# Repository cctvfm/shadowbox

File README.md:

# shadowbox
Shadowbox is an Open Source optically controlled digital drone synth where parameters are controlled by introducing or blocking light. Based on Emilie Gillet's Plaits Module.

To Compile code:

Copy entire 'neuzplaits' folder into the 'eurorack' folder in the mutable dev environment.

run 

make -f neuzplaits/bootloader/makefile hex

make -f neuzplaits/makefile

to upload using ST-Link V2:

make -f neuzplaits/makefile upload

'AVR CHICLET' is an alternate brain board using ATMEGA328P. Code to come.

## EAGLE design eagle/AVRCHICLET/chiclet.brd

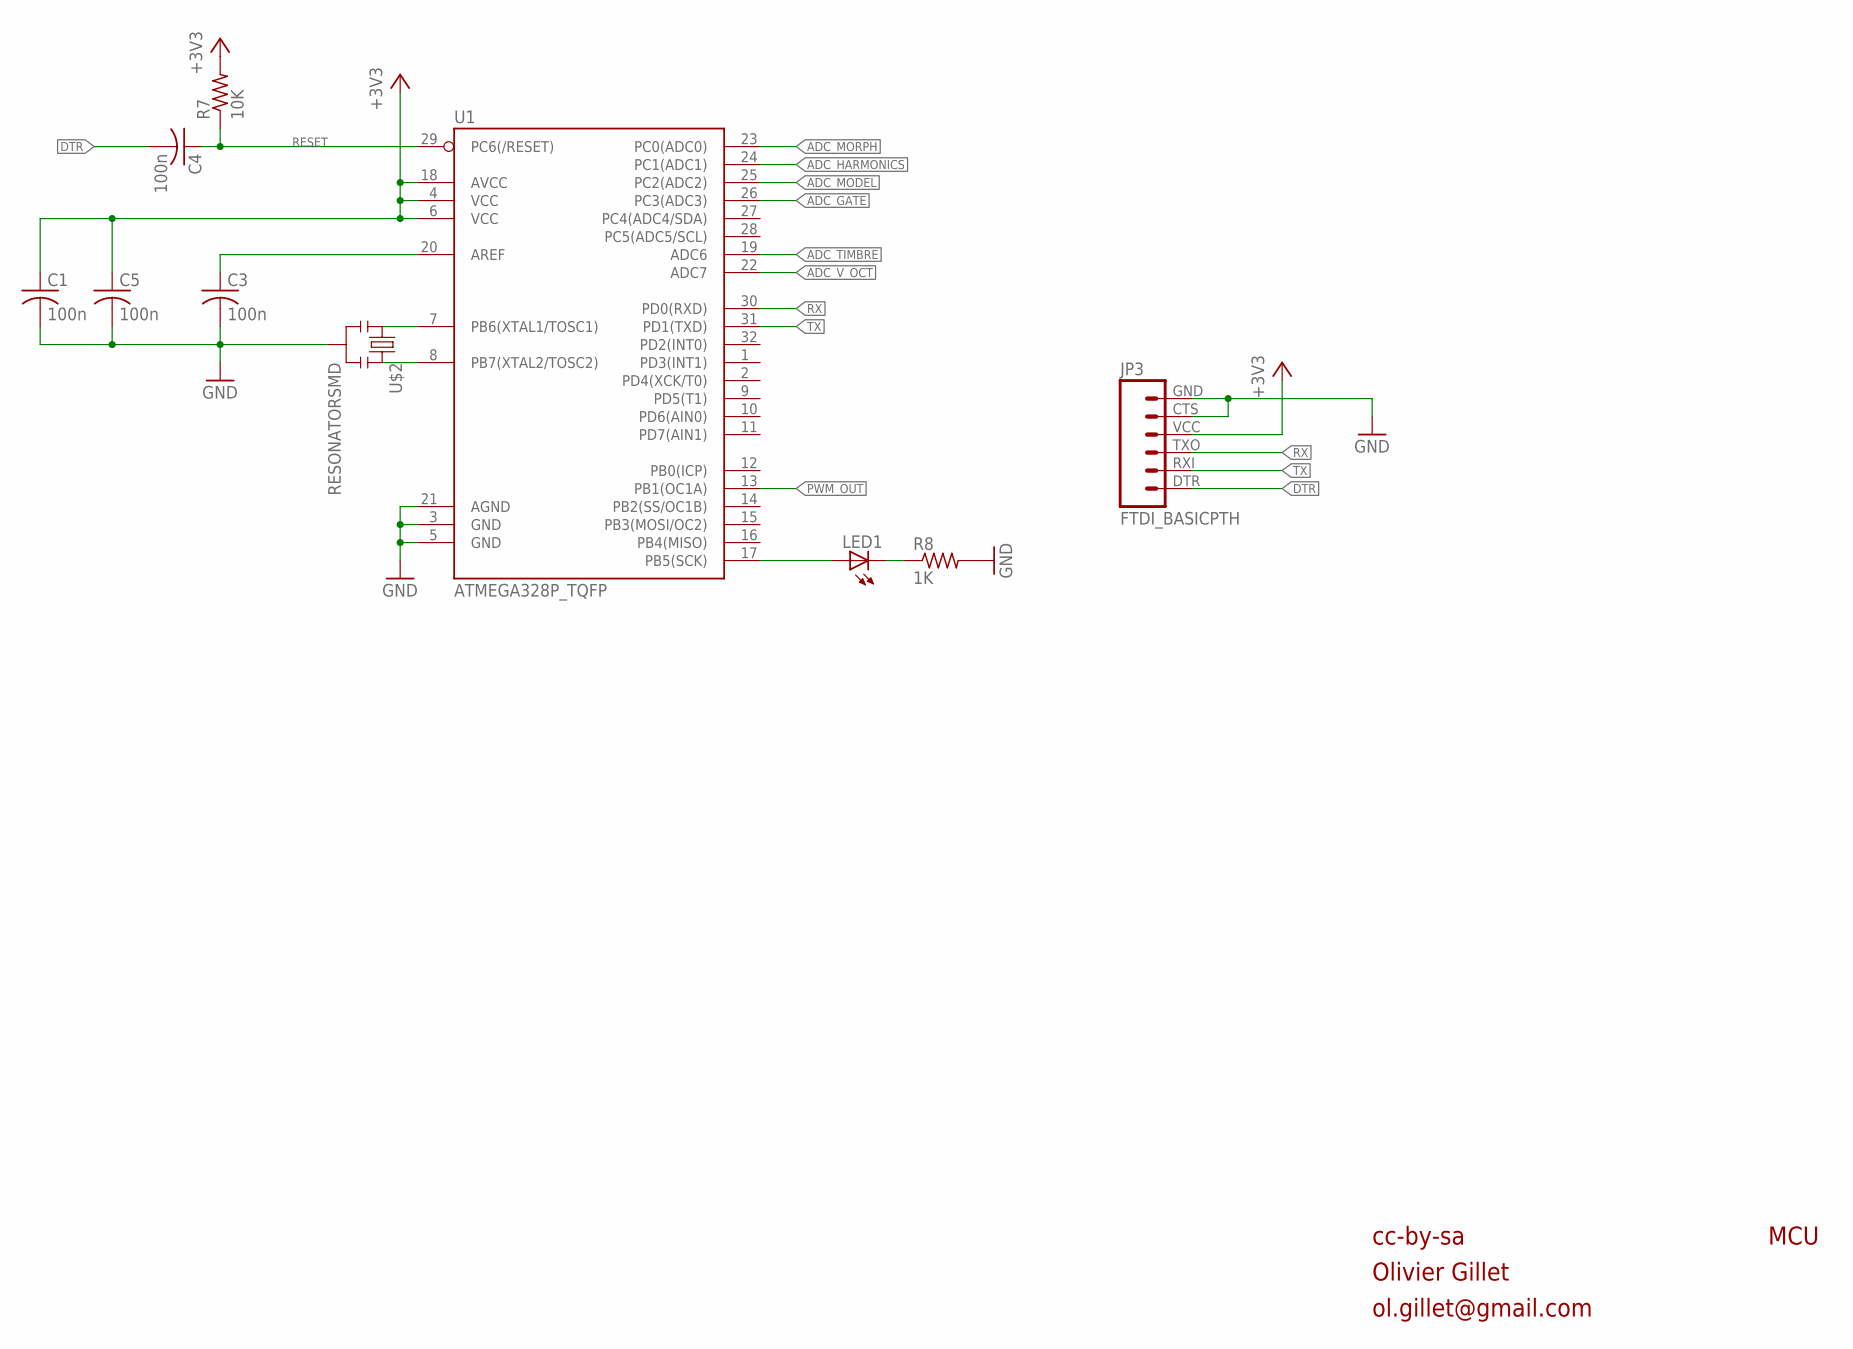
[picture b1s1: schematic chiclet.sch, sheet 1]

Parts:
C1, C3, C4, C5: 100n; C0805
JP3: FTDI_BASICPTH; FTDI_BASIC
LED1: LED-0805; LED-805
R7: 10K; M0805
R8: 1K; M0805
U1: ATMEGA328P_TQFP; TQFP32-08
U$2: RESONATORSMD; RESONATOR-SMD

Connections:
+3V3: C1.1, C5.1, JP3.VCC (4), R7.2, U1.4 (VCC), U1.6 (VCC), U1.18 (AVCC); also elsewhere on the board
ADC_GATE: U1.26 (PC3(ADC3)); also elsewhere on the board
ADC_HARMONICS: U1.24 (PC1(ADC1)); also elsewhere on the board
ADC_MODEL: U1.25 (PC2(ADC2)); also elsewhere on the board
ADC_MORPH: U1.23 (PC0(ADC0)); also elsewhere on the board
ADC_TIMBRE: U1.19 (ADC6); also elsewhere on the board
ADC_V_OCT: U1.22 (ADC7); also elsewhere on the board
DTR: C4.2, JP3.DTR (1)
GND: C1.2, C3.2, C5.2, JP3.CTS (5), JP3.GND (6), R8.2, U1.3 (GND), U1.5 (GND), U1.21 (AGND), U$2.2; also elsewhere on the board
unnamed: U1.7 (PB6(XTAL1/TOSC1)), U$2.1
unnamed: U1.8 (PB7(XTAL2/TOSC2)), U$2.3
unnamed: C3.1, U1.20 (AREF)
unnamed: LED1.A, U1.17 (PB5(SCK))
unnamed: LED1.C, R8.1
PWM_OUT: U1.13 (PB1(OC1A)); also elsewhere on the board
RESET: C4.1, R7.1, U1.29 (PC6(/RESET))
RX: JP3.TXO (3), U1.30 (PD0(RXD))
TX: JP3.RXI (2), U1.31 (PD1(TXD))

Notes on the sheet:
cc-by-sa
Olivier Gillet
ol.gillet@gmail.com
MCU

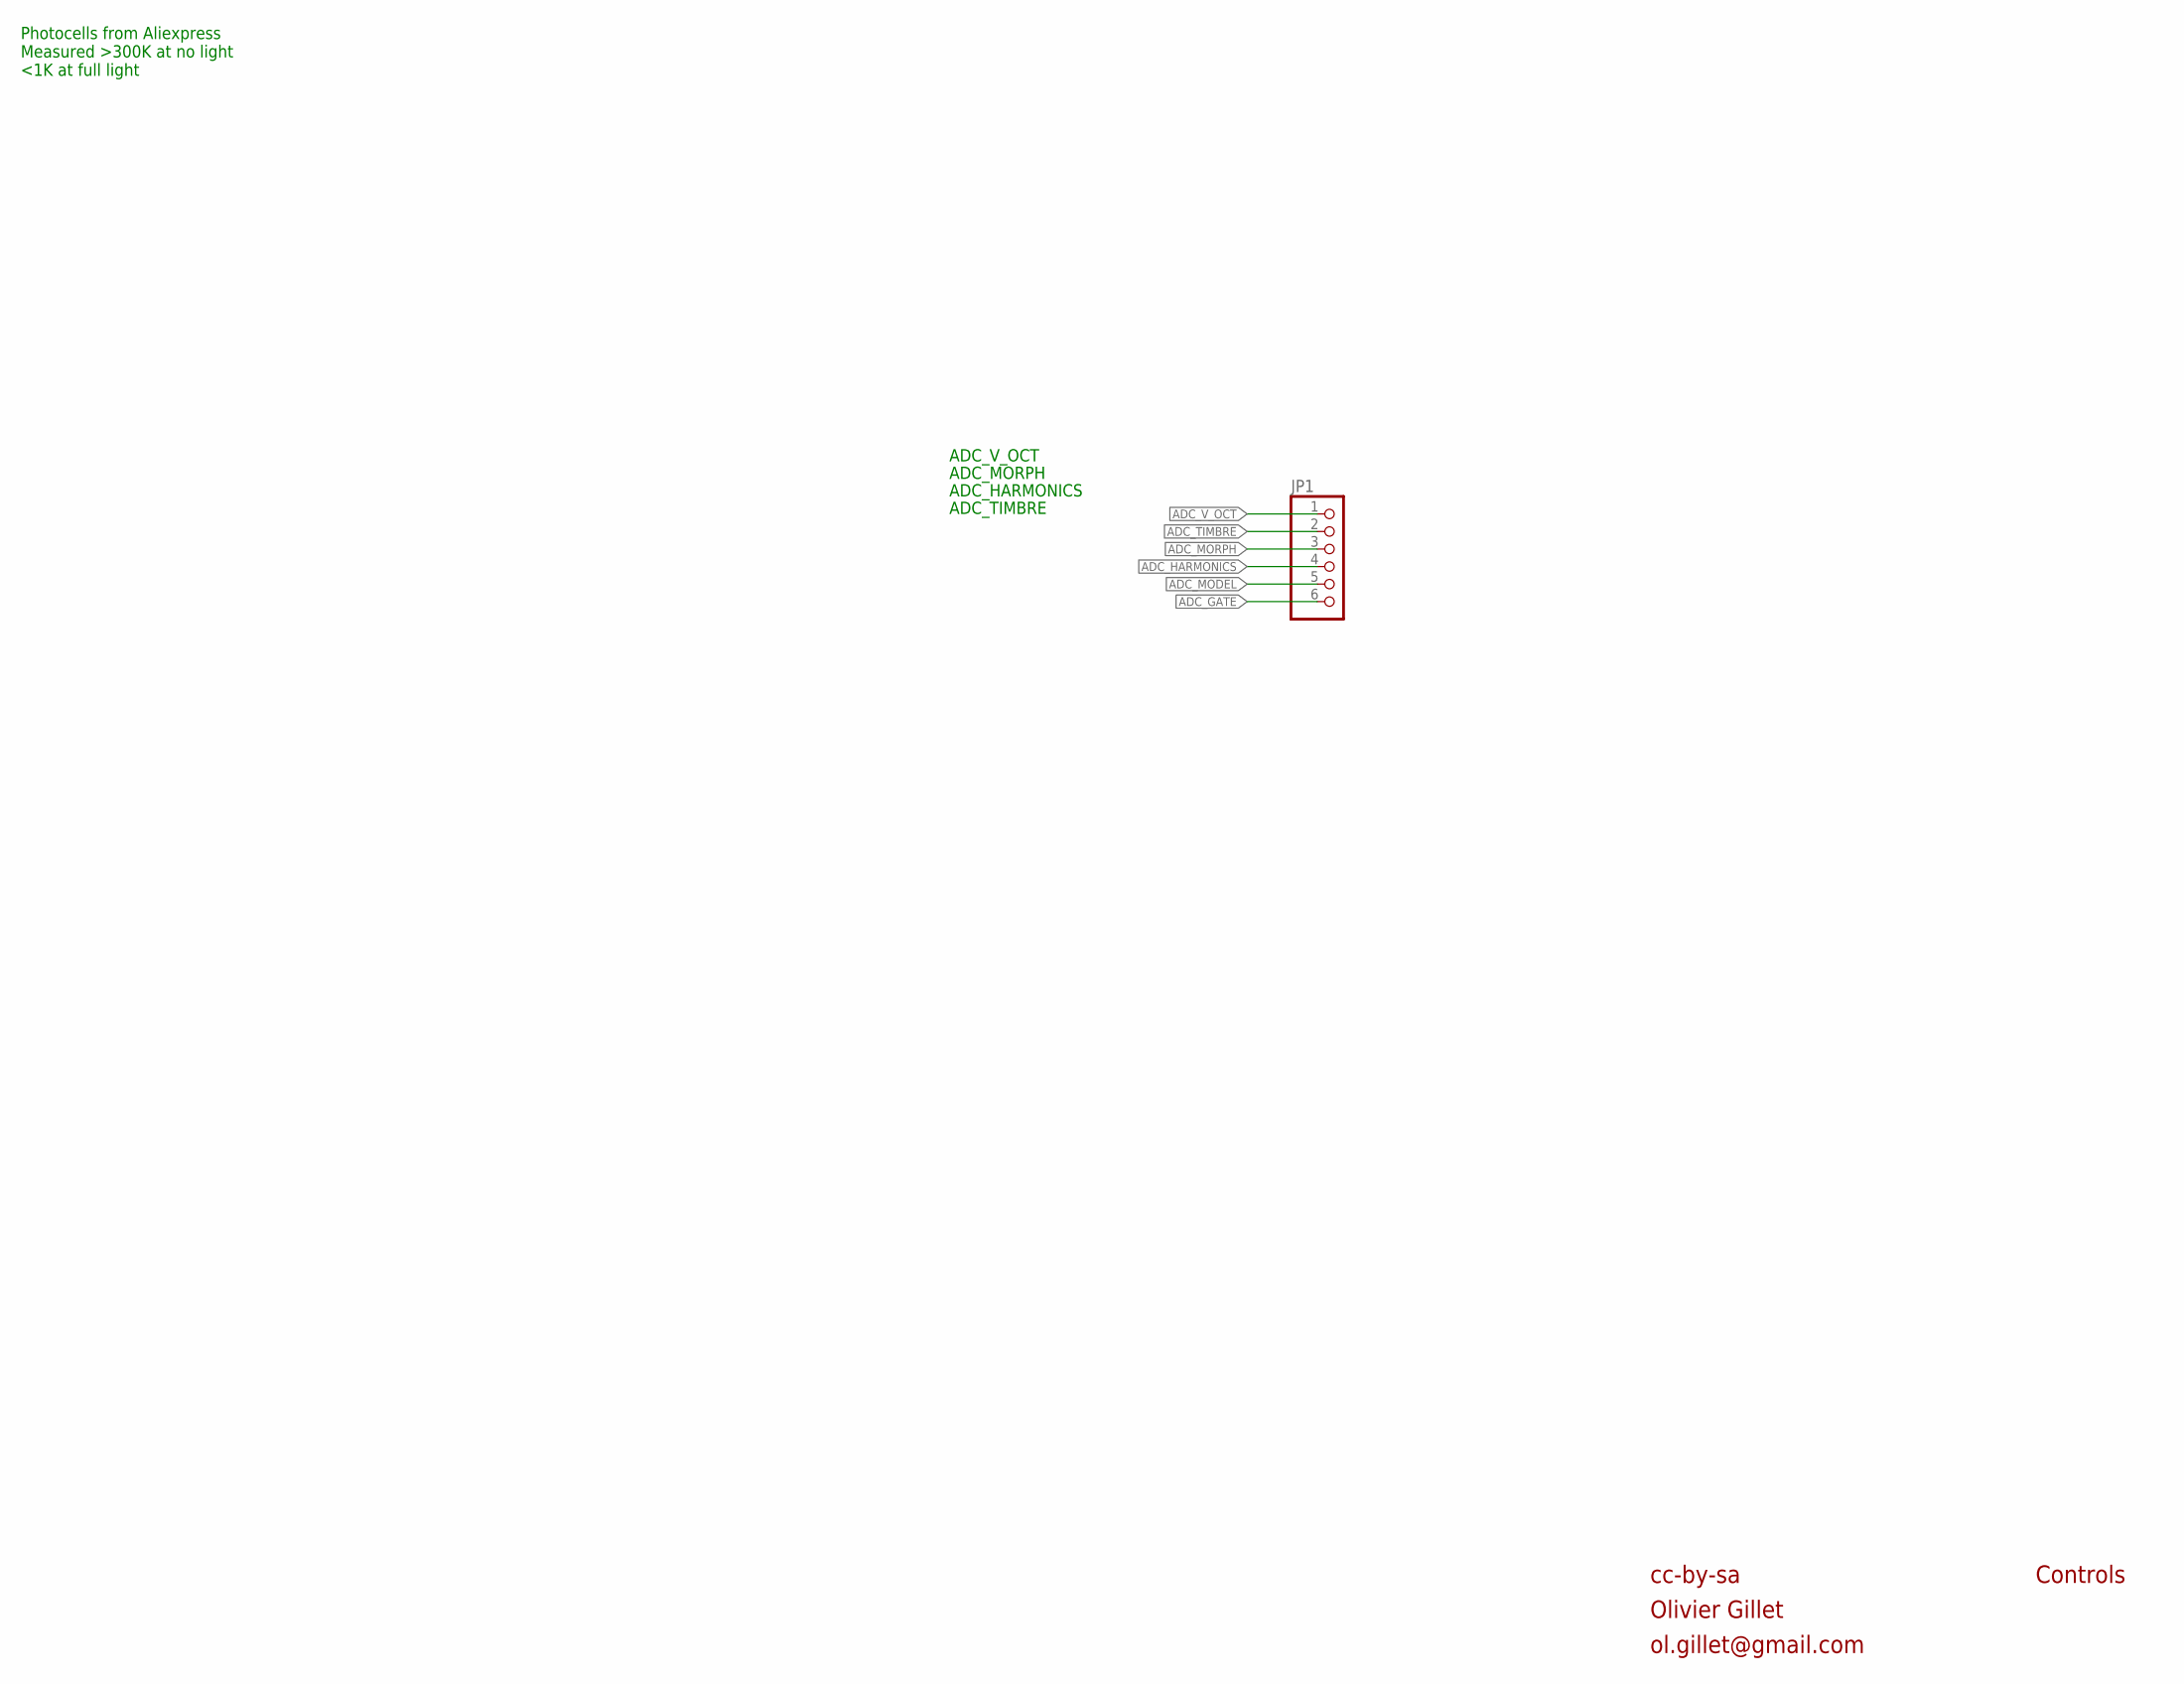
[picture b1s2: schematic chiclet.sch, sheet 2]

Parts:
JP1: PINHD-1X6; 1X06

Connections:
ADC_GATE: JP1.6; also elsewhere on the board
ADC_HARMONICS: JP1.4; also elsewhere on the board
ADC_MODEL: JP1.5; also elsewhere on the board
ADC_MORPH: JP1.3; also elsewhere on the board
ADC_TIMBRE: JP1.2; also elsewhere on the board
ADC_V_OCT: JP1.1; also elsewhere on the board

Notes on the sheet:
cc-by-sa
Olivier Gillet
ol.gillet@gmail.com
Controls
Photocells from Aliexpress Measured >300K at no light <1K at full light
ADC_V_OCT
ADC_MORPH
ADC_HARMONICS
ADC_TIMBRE

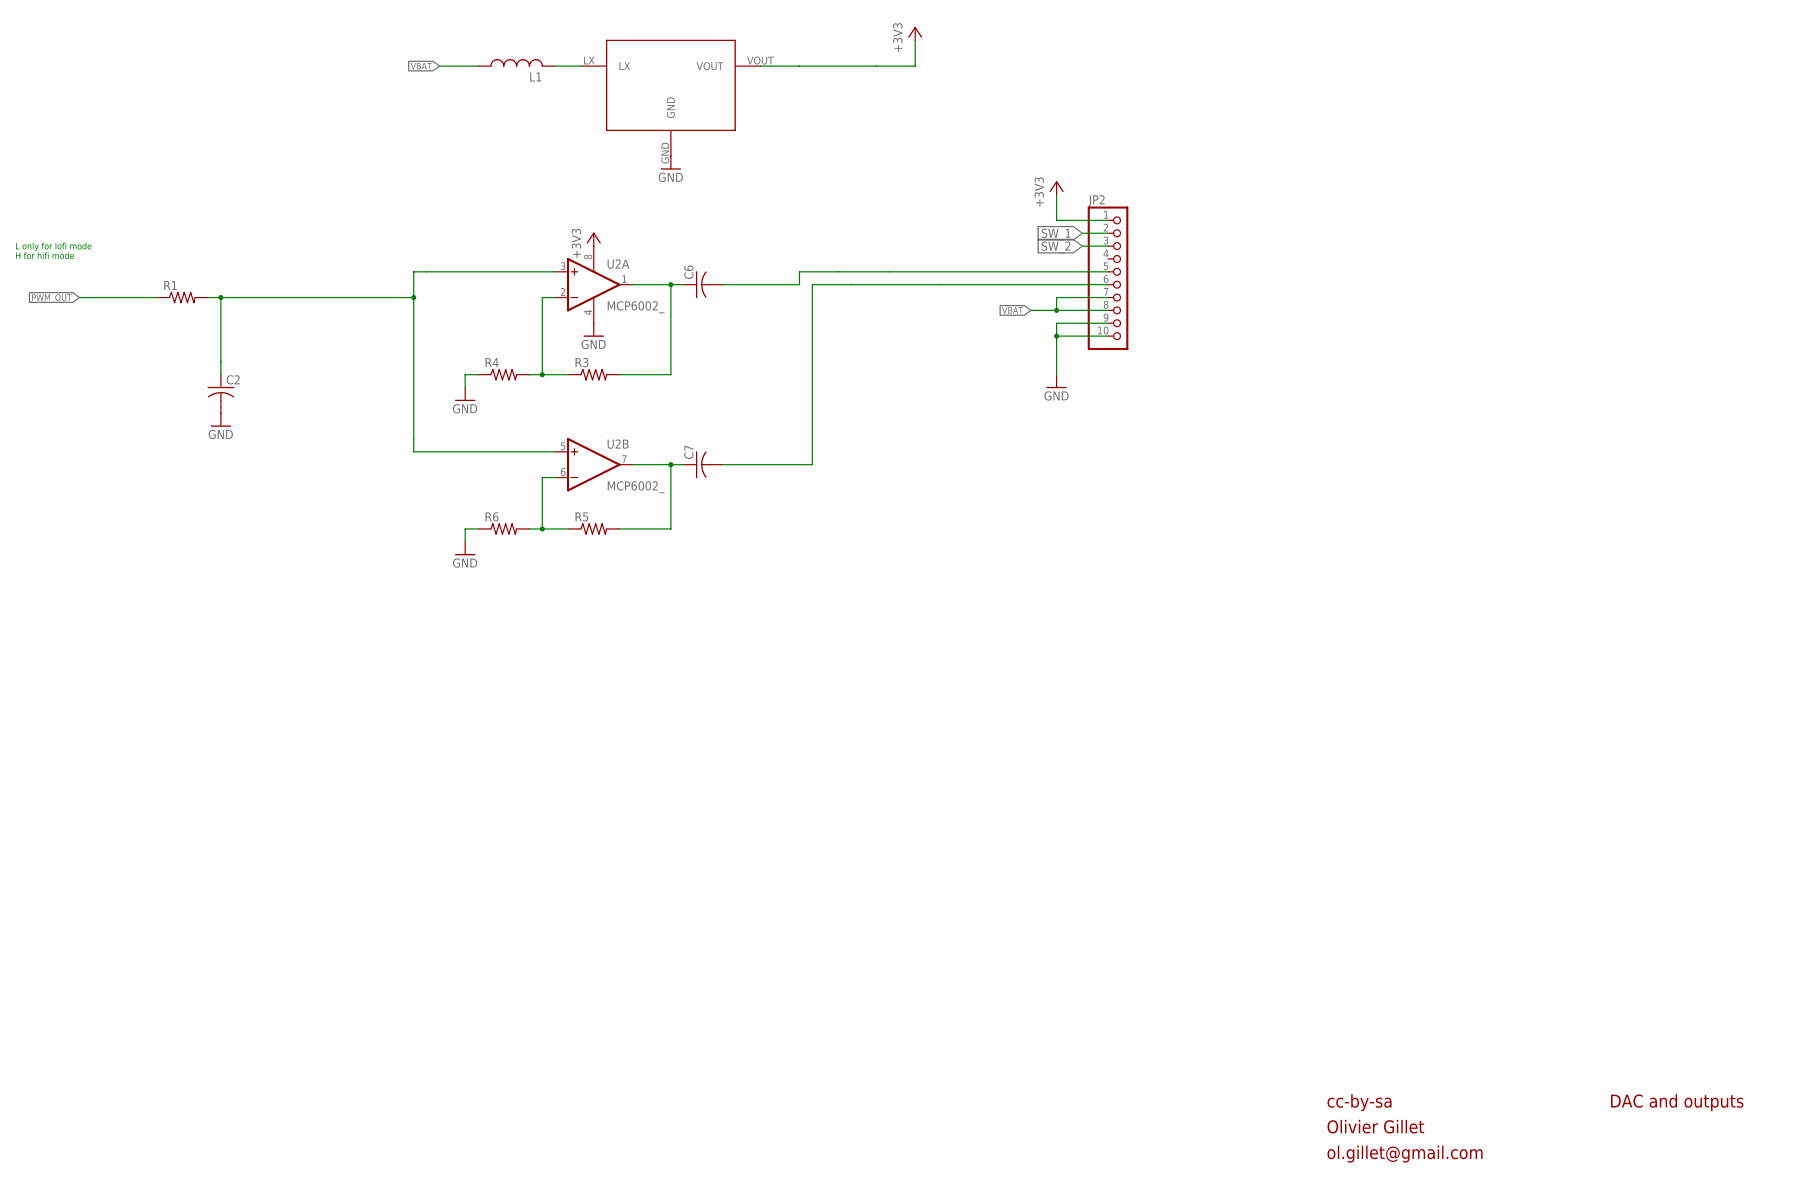
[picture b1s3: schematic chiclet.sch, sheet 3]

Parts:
C2, C6, C7: C-USC0805; C0805
JP2: PINHD-1X10; 1X10
L1: L-USL2825P; L2825P
R1, R3, R4, R5, R6: R-US_R0805; R0805
U2: MCP6002_; SO08
U$1: QX2304L33E; SOT89-R

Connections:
+3V3: JP2.1, U2.8 (V+), U$1.VOUT; also elsewhere on the board
GND: C2.2, JP2.9, JP2.10, R4.1, R6.1, U2.4 (V-), U$1.GND; also elsewhere on the board
unnamed: L1.2, U$1.LX
unnamed: C2.1, R1.2, U2.3 (+IN), U2.5 (+IN)
unnamed: C6.2, JP2.5
unnamed: C7.2, JP2.6
unnamed: R3.1, R4.2, U2.2 (-IN)
unnamed: R5.1, R6.2, U2.6 (-IN)
unnamed: C7.1, R5.2, U2.7 (OUT)
unnamed: C6.1, R3.2, U2.1 (OUT)
PWM_OUT: R1.1; also elsewhere on the board
SW_1: JP2.2
SW_2: JP2.3
VBAT: JP2.7, JP2.8, L1.1

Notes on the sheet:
cc-by-sa
Olivier Gillet
ol.gillet@gmail.com
DAC and outputs
L only for lofi mode H for hifi mode

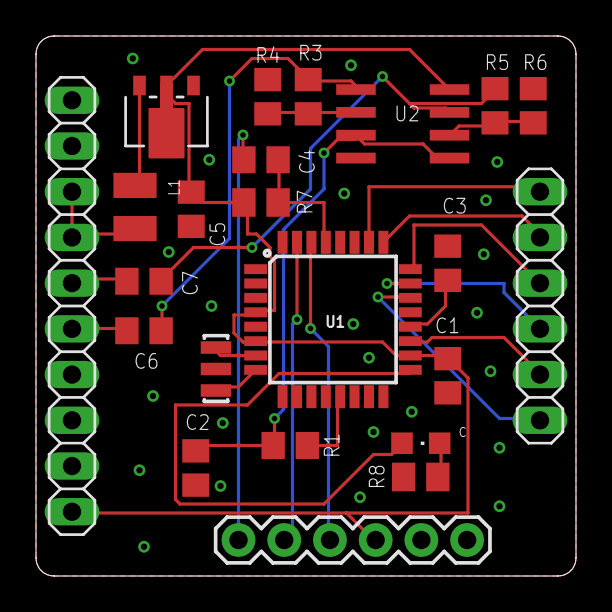
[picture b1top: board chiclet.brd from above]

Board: 2 copper layers, 30.0 x 30.0 mm, 23 parts (0 on the bottom side), 27 nets.

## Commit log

2021-10-28 Initial upload

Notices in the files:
parts and their libraries:
SparkFun-IC-Microcontroller: Licensing: Creative Commons ShareAlike 4.0 International - https://creativecommons.org/licenses/by-sa/4.0
